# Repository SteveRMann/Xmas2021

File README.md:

# XMAS_2020_Lights
  xmasTree2020: This is the light show for the outside Christmas tree.

2019:
We used xmas_tree_blend.ino for the inside tree before Christmas.
On Christmas day, I switched to XmasTree2_OTA.ino.

xmasTree2020.ino is based on xmasTree2_OTA.ino.

XmasTree2OTA.ino adds a single LED for the topper using a second data pin on the Wemos D1.
(Maybe merge some of the effects from xmas_tree_OTA.ino with XmasTree2OTA.ino).

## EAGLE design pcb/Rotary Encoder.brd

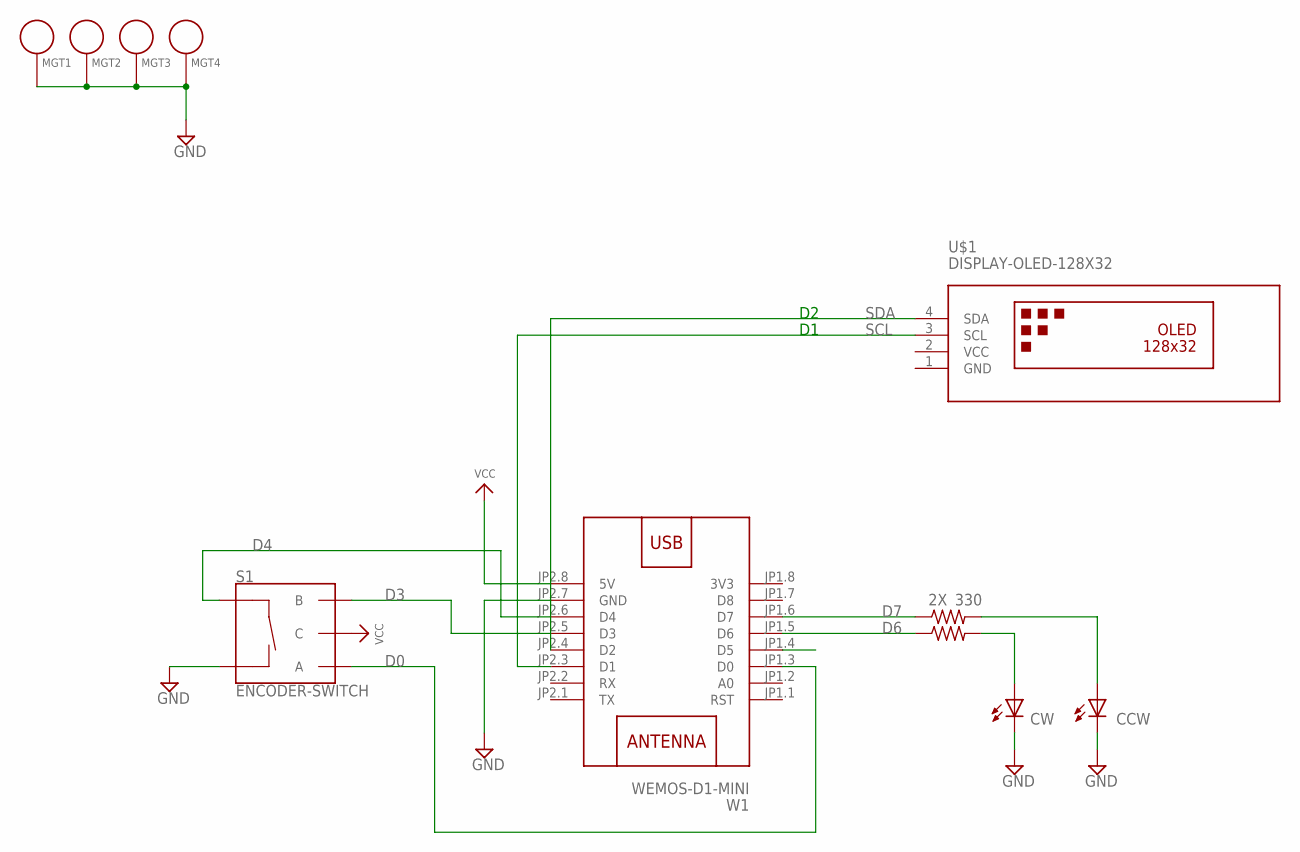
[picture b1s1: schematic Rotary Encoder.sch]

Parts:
2X, 330: R-US_0207/10; 0207/10
CCW: LED5MM
CW: LED5MM
MGT1, MGT2, MGT3, MGT4: BEAGLEBONEBLACK_MOUNTING_HOLE
S1: ENCODER-SWITCH; ROTARY_ENC_PLAIN
U$1: DISPLAY-OLED-128X32
W1: WEMOS-D1-MINI

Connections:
3V3: W1.JP1.8 (3V3)
D0: S1.A, W1.JP1.3 (D0)
D1: U$1.3 (SCL), W1.JP2.3 (D1)
D3: S1.B, W1.JP2.5 (D3)
D4: S1.SW+, W1.JP2.6 (D4)
D6: 2X.1, W1.JP1.5 (D6)
D7: 330.1, W1.JP1.6 (D7)
GND: CCW.K (C), CW.K (C), MGT1.P$1, MGT2.P$1, MGT3.P$1, MGT4.P$1, S1.SW-, U$1.1 (GND), W1.JP2.7 (GND)
unnamed: 330.2, CCW.A
unnamed: 2X.2, CW.A
SCL: W1.JP1.4 (D5)
SDA: U$1.4 (SDA), W1.JP2.4 (D2)
VCC: S1.C, U$1.2 (VCC), W1.JP2.8 (5V)

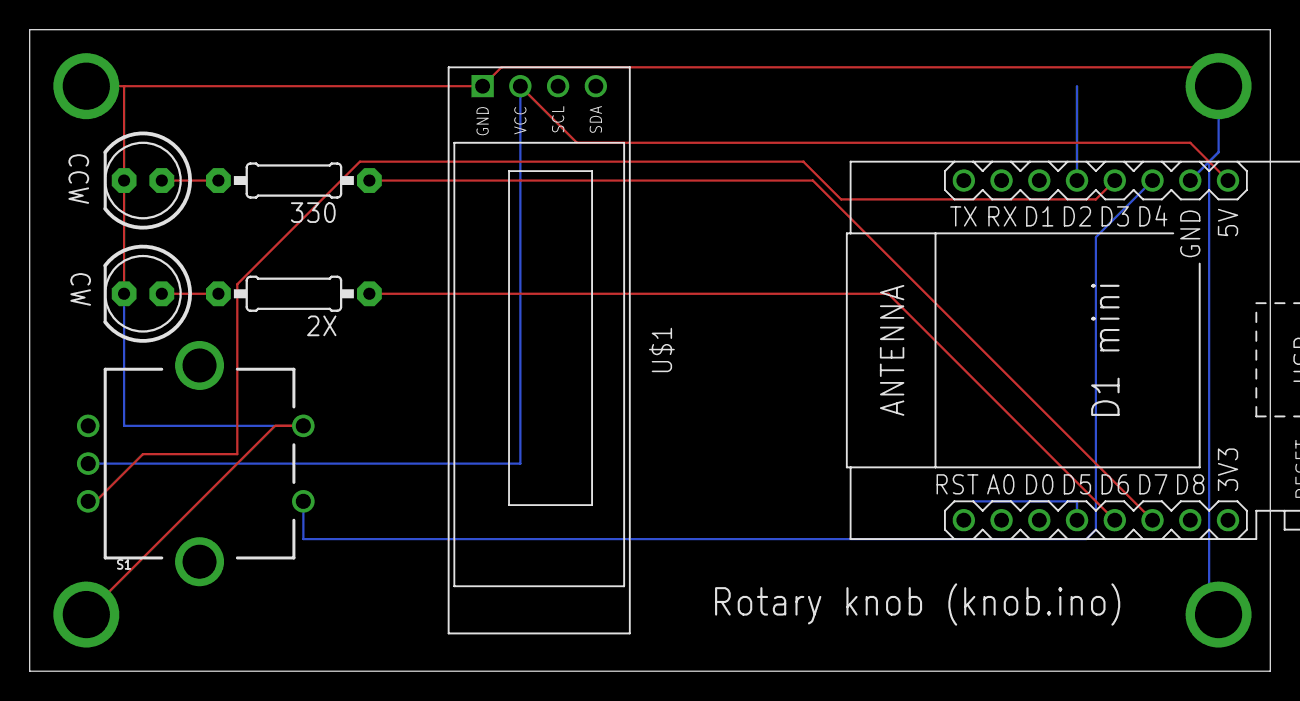
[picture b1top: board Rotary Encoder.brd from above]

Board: 2 copper layers, 83.5 x 43.2 mm, 11 parts (0 on the bottom side), 11 nets.

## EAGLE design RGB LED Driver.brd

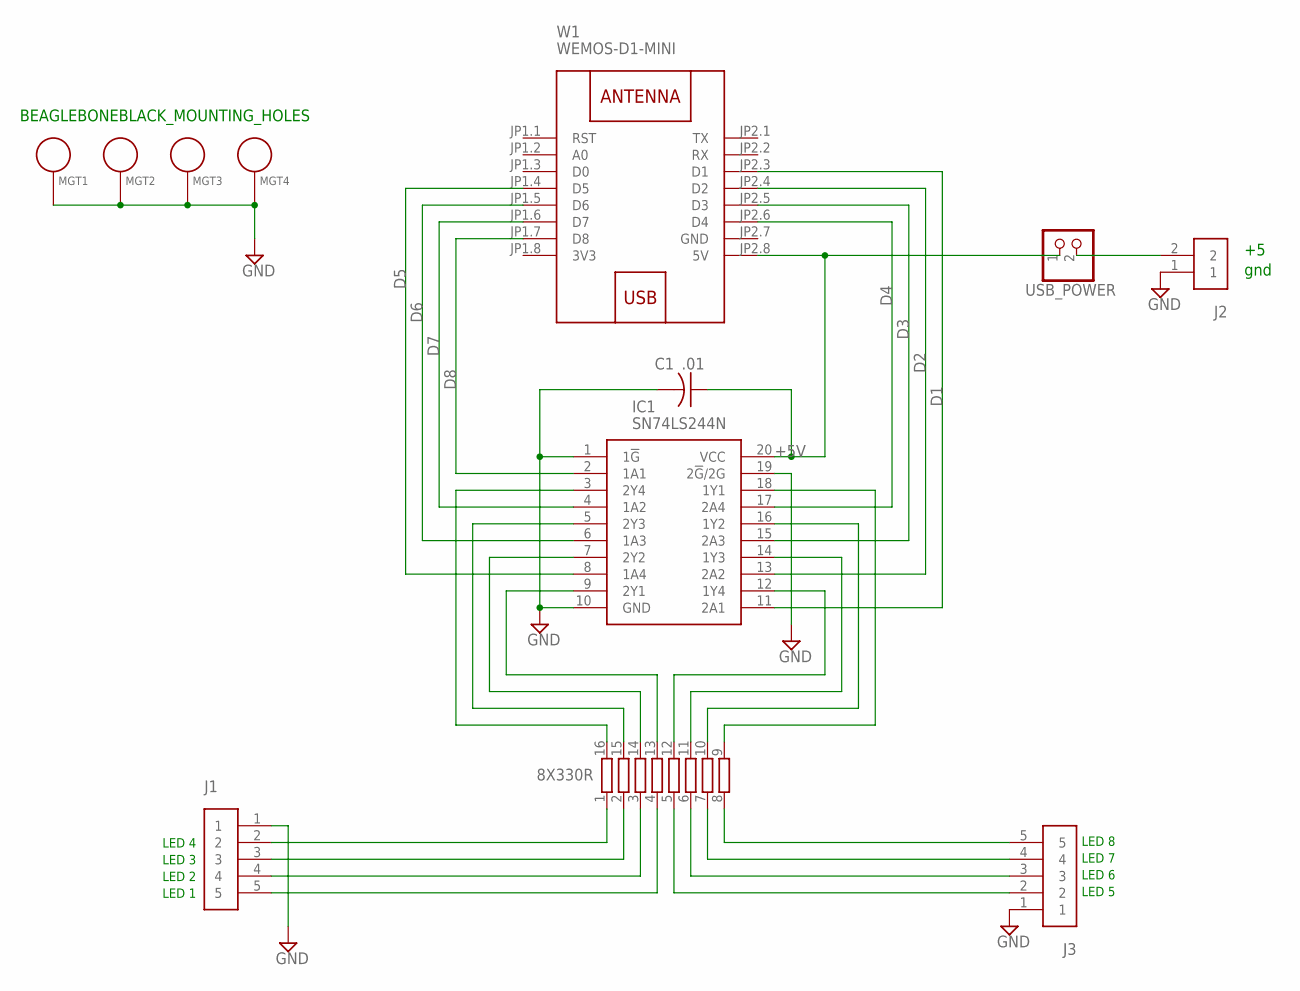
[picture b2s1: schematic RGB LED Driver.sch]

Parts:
8X330R: 2NBS16-8; SO16
C1: .01; C050-024X044
IC1: SN74LS244N; DIP794W53P254L2540H508Q20N
J1, J3: 691311400105; TERMINALBLOCK_PLUGGABLE-5-7.62MM
J2: 691311400102; TERMINALBLOCK_PLUGGABLE-2-7.62MM
MGT1, MGT2, MGT3, MGT4: BEAGLEBONEBLACK_MOUNTING_HOLE
USB_POWER: PINHD-1X2; 1X02
W1: WEMOS-D1-MINI

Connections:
3V3: W1.JP1.8 (3V3)
+5V: C1.1, IC1.20 (VCC), USB_POWER.1, W1.JP2.8 (5V)
D1: IC1.11 (2A1), W1.JP2.3 (D1)
D2: IC1.13 (2A2), W1.JP2.4 (D2)
D3: IC1.15 (2A3), W1.JP2.5 (D3)
D4: IC1.17 (2A4), W1.JP2.6 (D4)
D5: IC1.8 (1A4), W1.JP1.4 (D5)
D6: IC1.6 (1A3), W1.JP1.5 (D6)
D7: IC1.4 (1A2), W1.JP1.6 (D7)
D8: IC1.2 (1A1), W1.JP1.7 (D8)
GND: C1.2, IC1.1 (1!G), IC1.10 (GND), IC1.19 (2!G!/2G), J1.1, J2.1, J3.1, MGT1.P$1, MGT2.P$1, MGT3.P$1, MGT4.P$1, W1.JP2.7 (GND)
unnamed: 8X330R.12, IC1.12 (1Y4)
unnamed: 8X330R.11, IC1.14 (1Y3)
unnamed: 8X330R.10, IC1.16 (1Y2)
unnamed: 8X330R.9, IC1.18 (1Y1)
unnamed: 8X330R.8, J3.5
unnamed: 8X330R.7, J3.4
unnamed: 8X330R.6, J3.3
unnamed: 8X330R.14, IC1.7 (2Y2)
unnamed: 8X330R.13, IC1.9 (2Y1)
unnamed: 8X330R.5, J3.2
unnamed: 8X330R.15, IC1.5 (2Y3)
unnamed: 8X330R.16, IC1.3 (2Y4)
unnamed: J2.2, USB_POWER.2
unnamed: 8X330R.4, J1.5
unnamed: 8X330R.3, J1.4
unnamed: 8X330R.2, J1.3
unnamed: 8X330R.1, J1.2

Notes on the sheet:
LED 8
LED 7
LED 6
LED 5
LED 4
LED 3
LED 2
LED 1
BEAGLEBONEBLACK_MOUNTING_HOLES
gnd

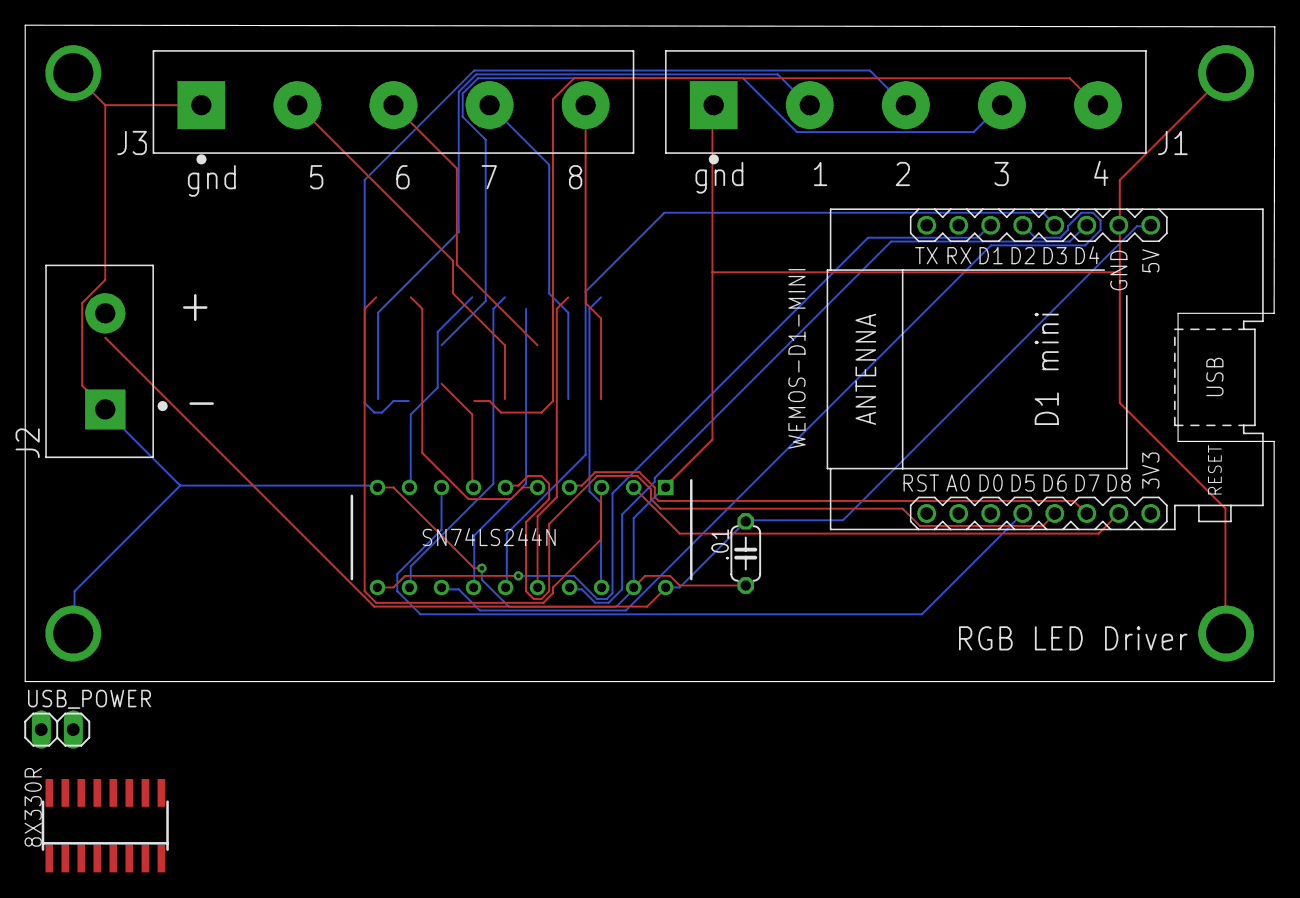
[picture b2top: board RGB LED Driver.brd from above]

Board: 2 copper layers, 99.1 x 52.1 mm, 12 parts (0 on the bottom side), 27 nets.

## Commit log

2020-11-28 Add files via upload
    Xmas2020 light show.
2020-11-28 Add files via upload
    Fixed hostname
2020-11-29 Added test sketch
2020-12-01 First light
2020-12-05 Add files via upload
    Experiments on arrays of rings of LEDs
2020-12-07 More demos added
2020-12-09 Removed timeObj from colorRings.ino
2020-12-09 Fixed the top_glitter function, added dlay function.
2020-12-09 Removed unused tab, redundant colors.
2020-12-10 Fixed top_glitter
2020-12-12 Added MQTT
2020-12-23 Added diagnostic MQTT topics
    Diagnostics by MQTT messages allow for addressed LEDs to be turned on. Used to get the LED number of a failing LED.
    (For example one with no green).
    See the companion program, knob.ino
2020-12-23 Updated notes.txt
2020-12-23 Added knob.ino
    This is a diagnostic sketch to light selected LEDs.
2020-12-23 Using dlay library, added diagnostic timeout.
2020-12-24 Added timeout to the diagnostics
2020-12-24 Added MQTT holdTopic
    Message is the hold time between colors.
2020-12-24 Bug fix in diagnostic mode
    Fixed a bug where the drip timers were still running while in the diagnostic mode.
2020-12-25 Added OLED display
2021-11-16 Added schematic and board
2021-11-24 Mid-project updates
2021-11-29 Periodic updates
    Fixed OTA in TwinkleFox and Pacifica
2021-12-22 Reassign D1, D2

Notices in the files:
parts and their libraries:
diy-modules: Released under the Creative Commons Attribution 4.0 International License: http://creativecommons.org/licenses/by/4.0
SparkFun-Switches: Licensing: Creative Commons ShareAlike 4.0 International - https://creativecommons.org/licenses/by-sa/4.0
